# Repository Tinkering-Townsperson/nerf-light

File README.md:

# Nerf Light

Linear Red light green light game with CV Nerf turret.

## Demo videos (Click to open video on youtube.com)

## What this is

So you've watched Squid Game before, right?....

If not, that's okay. "Red light green light" is a game where one person decides whether it's "green light" or "red light". When it's green light, the deciding person must not look at the players, while the players travel towards the deciding person. When the deciding person announces "red light", all players must halt any movement immediately. The deciding person must turn around quickly, seeing if anyone moved. Should someone move during this phase, they will be eliminated.

The TV show "Squid Game" introduces a verry deadly twist to this game: people now get shot to death if they fail in the game. This is exactly what we're trying to create.

The camera tracks people and detects movements. If a person is detected moving during red light, a beefy servo motor attached to the trigger will turn fire the (Nerf) gun (and kill the person :-[)

We encountered a technical difficulty because apparently the most powerful motor is not powerful enough to move the gun... we pivoted from the original idea to make a linear red light green light. So how is it different from the original red light green light?

1. No to (disgusting) friends
   It cannot work with your friends. Why do you have friends anyway? What are you doing? Socialising?! Impossible!!!111!!!
2. It's in a line.
   Since the gun no longer moves, you have to move towards the gun while following a straight line. Discipline yourself!!!1111!!!!

When the players reach the gun, they can press a button to end and win the game.

## Why we built this

We built this for Undercity, so we decided to build something very cool, something that people will like. With the recent Squid Game 3 releasing, I'm certain that this little invention will become very popular...

## Photo gallery

## Wiring Diagram

Keep in mind you also need to plug a USB webcam into a USB port on the pi.

## BOM

| Part name | Quantity |
| --- | --- |
| Raspberry 3B+ (or any Pi) | 1 |
| Red LED (generic) | 1 |
| Green LED (generic) | 1 |
| 400Ω Resistor | 2 |
| Electric Nerf gun (any) | 1 |
| Beefy servo motor (MG996R) | 1 |
| Stepper motor (ended up not using) | 1 |
| Stepper driver board (ended up not using) | 1 |
| Large button | 1 |
| USB Web Camera | 1 |

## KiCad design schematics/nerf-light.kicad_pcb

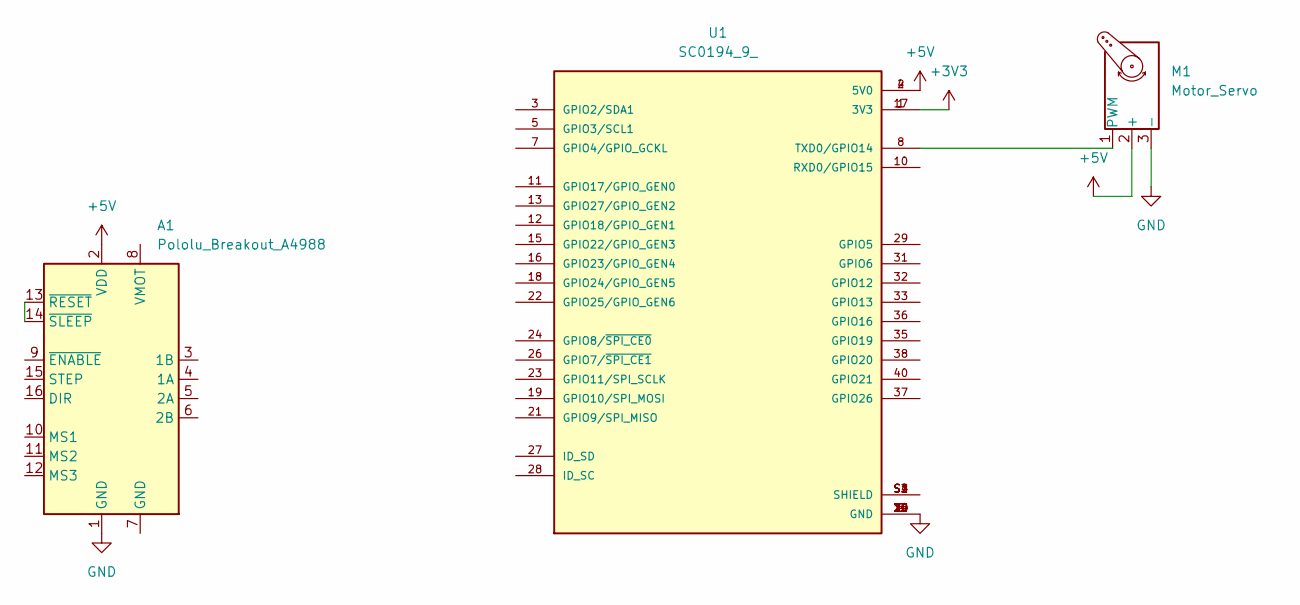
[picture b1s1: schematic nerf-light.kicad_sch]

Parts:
A1: Pololu_Breakout_A4988; Pololu_Breakout-16_15.2x20.3mm
M1: Motor_Servo; PinHeader_1x03_P1.00mm_Horizontal
U1: SC0194_9_; MODULE_SC0194_9_; PARTREV 1.0; DigiKey_Part_Number 2648-SC0194(9)-ND

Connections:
+3V3: U1.1 (3V3), U1.17 (3V3)
+5V: A1.2 (VDD), M1.2 (+), U1.2 (5V0), U1.4 (5V0)
GND: A1.1 (GND), M1.3 (-), U1.6 (GND), U1.9 (GND), U1.14 (GND), U1.20 (GND), U1.25 (GND), U1.30 (GND), U1.34 (GND), U1.39 (GND)
unnamed: A1.13 (~RESET), A1.14 (~SLEEP)
unnamed: M1.1 (PWM), U1.8 (TXD0/GPIO14)
unnamed: U1.S1 (SHIELD), U1.S2 (SHIELD), U1.S3 (SHIELD), U1.S4 (SHIELD)

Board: 2 copper layers, 3 parts (0 on the bottom side), 6 nets, no tracks yet.

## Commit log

2025-07-12 feat: Initial commit
2025-07-12 feat: Camera boilerplate
2025-07-12 feat: Add GPIO dependency
2025-07-13 Add 65mm MG996R "beefy servo" arm 3D printing file
2025-07-13 feat: Upload KiCad schematic so far
2025-07-13 refactor: Organise and improve code
2025-07-13 feat: Add debug mode
2025-07-13 feat: Upgrade model
2025-07-13 fix: Add back print statement
2025-07-13 fix: Correct model filename
2025-07-13 fix: Everything
2025-07-13 chore: Add KiCad ignores
2025-07-13 feat: Update schematic
2025-07-13 fix: Fix some assorted things
2025-07-13 Feature: Implement Motion Detection System
2025-07-13 Task: Clean the code
2025-07-13 Most likely broken code...
2025-07-13 Revert "Most likely broken code..."
    This reverts commit 7a617165085cbfe3920aafb5688168040b9af865.
2025-07-13 Update stepper test
2025-07-13 style: Make some visual changes
2025-07-13 feat: Implement stepper motor class
2025-07-13 feat: Add debug statement
2025-07-13 feat: Update test code
2025-07-13 fix: Add pigpio to dependencies
2025-07-13 fix: Remove leftover testing code
2025-07-13 fix: Use absolute value
2025-07-13 feat: Genetically modify stepper motor
2025-07-13 fix: Make motor use shortest path
2025-07-13 fix: Put the prompt in the bag
2025-07-14 Feature: Add simple (likely broken) angle claculations.
2025-07-14 update motor
2025-07-14 fix: Remove vibes
2025-07-14 feat: Fix some code for demos
2025-07-14 Start README
2025-07-14 Remove how to build
2025-07-14 Change to linear
2025-07-14 Add lax BOM
2025-07-14 feat: Pivot plan completely
2025-07-14 feat: Some stuff too tired
2025-07-14 fix: Remove extra argument
2025-07-14 feat: Abstract game_over
2025-07-14 fix: Bazongles
2025-07-14 fix: Oopsies hehe
2025-07-14 fix: OMG WHAT THE CTHRDFYHUGTRF%^YUHJMGFTY IS THIS
2025-07-14 fix: idk at this point i just wanna be done :(
2025-07-14 fix: Button implemented
2025-07-14 fix: something
2025-07-29 fix: I don't remember what this fixed but commiting anyways 🤷
2025-07-29 docs: Fix style/typos ig
2025-07-29 docs: Add BOM to README
2025-07-29 docs: Add demo videos
2025-07-29 docs: Add images, update BOM
2025-07-31 fix: Update BOM
2025-07-31 docs: Add wiring diagram
